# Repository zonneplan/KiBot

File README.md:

# KiBot (formerly KiPlot)

KiBot is a program which helps you to generate the fabrication and
documentation files for your KiCad projects easily, repeatable, and most
of all, scriptably. This means you can use a Makefile to export your
KiCad PCBs just as needed, or do it in a CI/CD environment.

For more information consult the [documentation](https://kibot.readthedocs.io/en/latest/) (hosted by Read the Docs)

If you want to see an example of what KiBot can generate visit this
[project](https://inti-cmnb.github.io/kibot_variants_arduprog_site/Browse/t1-navigate.html)

If this is the first time you read about KiBot, and you prefer to be
introduced listening to a podcast, you can try the following
(english audio, english and spanish subtitles available):

Here is another podcast, more centered on the CI/CD side:

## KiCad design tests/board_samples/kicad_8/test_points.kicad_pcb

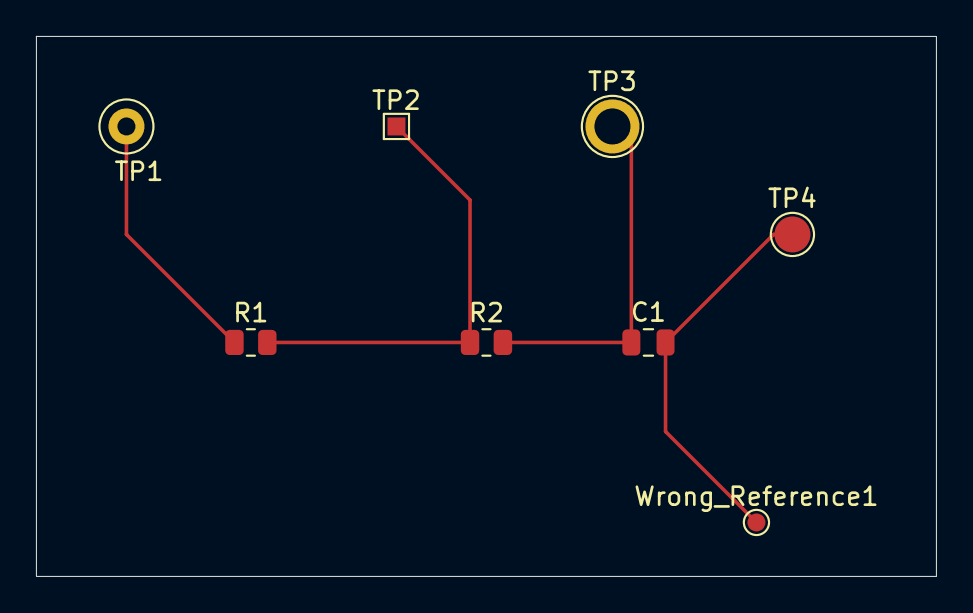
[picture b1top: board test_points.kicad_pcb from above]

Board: 2 copper layers, 50.0 x 30.0 mm, 8 parts (0 on the bottom side), 4 nets.

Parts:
C1: 1uF; C_0805_2012Metric
R1: 10; R_0805_2012Metric
R2: 20; R_0805_2012Metric
TP1: TestPoint; TestPoint_Loop_D1.80mm_Drill1.0mm_Beaded
TP2: TestPoint_Alt; TestPoint_Pad_1.0x1.0mm
TP3: TestPoint_Flag; TestPoint_Plated_Hole_D2.0mm
TP4: TestPoint_Probe; TestPoint_Pad_D2.0mm
Wrong_Reference1: TestPoint_Small; TestPoint_Pad_D1.0mm

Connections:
unnamed: C1.1, R2.2, TP3.1
unnamed: C1.2, TP4.1, Wrong_Reference1.1
unnamed: R1.1, TP1.1
unnamed: R1.2, R2.1, TP2.1

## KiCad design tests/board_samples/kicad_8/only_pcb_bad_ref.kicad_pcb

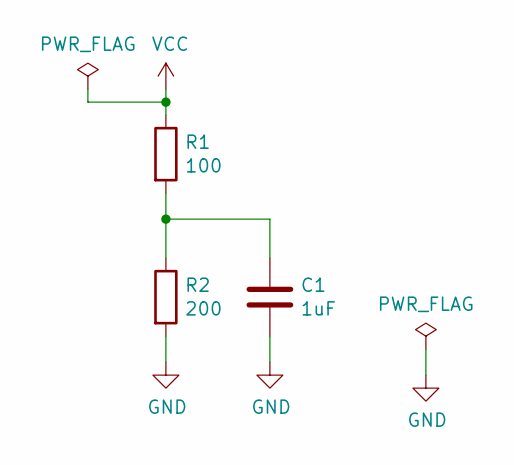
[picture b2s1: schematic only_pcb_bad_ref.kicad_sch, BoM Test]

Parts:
C1: 1uF; C_0805_2012Metric
R1: 100; R_0805_2012Metric
R2: 200; R_0805_2012Metric

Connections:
GND: C1.2, R2.2
unnamed: C1.1, R1.2, R2.1
VCC: R1.1

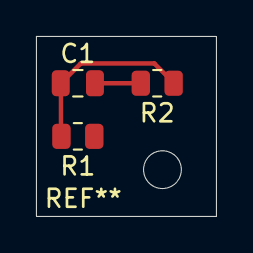
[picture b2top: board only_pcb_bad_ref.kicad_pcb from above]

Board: 2 copper layers, 10.0 x 10.0 mm, 3 parts (0 on the bottom side), 2 nets.

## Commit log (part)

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2024-07-11 [Print PCB][Fixed] Now the layers are always a list
2024-07-11 [iBoM Variants] Better debug info
2024-07-11 [Panelize][Fixed] PanelizeCopperfill.layers initialization
    Members supporting lists must be Optionable
2024-07-11 [Filters][Generic][Fixed] keys processing
    No longer visible as string
2024-07-11 [KiBoM] Simpler lcsc_link code for boolean
2024-07-11 [DOCs][Updated] Filter rotation and generic
2024-07-11 [BoM][Diff] Simplifications now that strings are promoted
2024-07-12 [Preflights] First draft for a fields checker
    See #643
2024-07-15 [Check Fields] Made more configurable the severity actions
2024-07-15 [Render 3D] Made the double trim optional
    Related to #644
2024-07-15 [DOCs] Now preflight docs are in individual documents
2024-07-16 [DOCs] Updated the E/DRC filters explanation
    Fixes #639
2024-07-17 [Windows][macOS] KiCad plug-in detection
    See #642
2024-07-17 [Filters][Added] separate_pins: used to create testpoint reports
    Closes #638
2024-07-17 [Tests] Image Magic site still down
2024-07-19 [DOCs] Separated the filter in individual docs
2024-07-19 [Added] Templates to generate testpoint reports
    Related to #638
2024-08-05 [DOCs] Updated drc_exclusions_workaround help
    Made clear that KiCad 8 solves the original problem.
    See #645
2024-08-05 [Flake8][Fix] C420: Unnecessary dict comprehension
    Rewrite using dict.fromkeys().
2024-08-05 [Tests] ImageMagick site back on line
2024-08-05 [Variants][Fixed] Problems when using `set_text_variables_before_output`
    Fixes #649
2024-08-06 [BoardView][Added] Support for BVR format
    From upstream code
2024-08-06 [Tests] Forced
2024-08-07 [DOCs][Updated] _field_* documentation
2024-08-07 [DOCs][Updated] Options marked as case insensitive
2024-08-07 [Optionable] _init_from_defaults is now the default
2024-08-07 [BoM] Default fit_field is now lowercase
2024-08-07 [DOCs][Updated] Defaults that promote dict -> list(dict)
2024-08-08 [DOCs][Updated] cases where fixed list len was applied
2024-08-08 [GUI][Added] Fixed len lists restrictions
2024-08-09 [GUI][Fixed] list(string)|string initialization issues
    - Renamed to "string_s"
    - Make it use the value from the tree
    - Also forced list(string) DataTypes to use the value from the tree
    - Correctly accept single strings
2024-08-13 [GUI] Sort the list of available preflights
2024-08-14 [DOCs][Updated] Changes in preflight defaults
2024-08-14 [Optionable] Support for [] as default for list(dict)
2024-08-14 [Filters] Moved the compiled regex to _regex
    Cleaner string representation
2024-08-14 [Preflights][Added] String representation
    For cases that aren't just a boolean
2024-08-14 [GUI][Added] dict|list(dict) -> dict_s
2024-08-16 [GUI] When choosing from a list with one element just return it
2024-08-19 [Changed] Stronger workaround for KiCad PCB text cache
    Fixes issues with external tools when not using variants
    Fixes #652
2024-08-19 [Fixed] Pre-flights configured before listing
    Now they have more complex strings that needs configured values
2024-08-19 [Changed] Code to reset the current config moved to a function
2024-08-20 [Changed] Now we keep a copy of the global options tree
2024-08-20 [Changed] extra argument for generate_outputs
    We don't use it
2024-08-20 [GUI][Run][Fixed] Reset the done status before run
2024-08-21 [Added] Dialog to see collected warnings
2024-08-21 [DOCs] Splitted the preflights
    Also sorted the dict types to make it reproducible
2024-08-22 [DOCs][Added] A couple of things KiBot can do
2024-08-22 [DOCs][Internal][Added] Some notes about defaults
2024-08-23 [Fixed] QR Lib output could also remove the exclusions
2024-08-23 [GUI][Fixed] We must ensure the globals are configured
    Not true when no config is loaded
2024-08-23 Allow to detect we never loaded globals
2024-08-23 [GUI][Added] Allow to start without config and/or sch/PCB
2024-08-23 [GUI][Added] Offer to save on exit
2024-08-26 [GUI][Added] Splash screen
    So the user knows we already started
2024-08-26 [GUI][Fixed] PCB file name ... used the SCH
2024-08-27 [GUI] New outputs are created with an unique name and some comment
2024-08-28 [3D Outputs][Fixed] Temporal .kicad_dru file not removed
    Fixes #655
2024-09-02 [GUI][Test] First regression test
    Created injecting events and using a virtual X server
2024-09-05 [GUI][list(string|dict)][Fixed] Initialization
    We need to fill the client data even for strings
2024-09-05 [GUI][Fixed] edited status notification
    Must always reach the parents, we can't assume they have the same
    perspective
2024-09-06 [CI/CD] Unified up/download-artifacts versions (v4)
2024-09-06 [CI/CD][Changed] Now we must explicitly include hidden files
    in artifats
2024-09-09 [DOCs][Filters][Added] error value example
2024-09-09 [Tests][GUI][Added] Preflights test
2024-09-09 [Tests][GUI][Added] Filters test
2024-09-09 [Test][GUI][Added] Variants test
2024-09-10 [Report][Fixed] Division by 0 when no nets are defined
2024-09-11 [Tests][GUI][Added] Groups test
2024-09-12 [Fixed][Render 3D] Rotation/offset for highlighted bottom components
    Fixes #659
2024-09-13 [Tests][CI/CD] Adjust to 8.0.4 render 3d variant 1 test reference
2024-09-13 [GUI] Better incremental search
2024-09-13 [GUI] Adjust the list of groups dialog when adding a new one
2024-09-13 [GUI][Test][Fixed] Problems using standard ids
2024-09-16 [SCH/PCB save][Fixed] Problems with huge constructs
    - In particular zone fills that can be bigger than 1 MB
    - KiCad seems to support lines of upto 1 MB
    - Now we split everything, like KiCad 8 does
    Fixes #660
2024-09-17 [DOCs] Updated docker image versions
2024-09-17 [GUI][Added] Help skeleton
2024-09-18 [DOCs][Updated] CLI options
2024-09-18 [DOCs][Test][Updated] Stats
2024-09-18 [Tests][Added] Separate pins to the GUI filters test
2024-09-18 [DOCs][Fixed] pcbdraw.remap is a string_dict (not a regular dict)
2024-09-18 [GUI][Added] Help for most of the GUI
    JUst opening a browser with the relevant docs section
2024-09-19 [DOCs][Added] Link to podcast introducing KiBot advantages
    AI generated by Google's NotebookLM
2024-09-19 [DOCs][Added] The podcasts to the GitHub README.md
2024-09-19 [DOCs] And another one ...
2024-09-23 [YAML examples][Added] Very simple use of 3D Render top
2024-09-23 [Blender Export][Fixed] Stacked boards
    When using an automatically generated PCB3D
2024-09-24 [PCB Print][Fixed] errors when printing a fully empty layer
2024-09-25 [Updated] KiBot media
2024-09-25 [CI/CD][Release] Changes to avoid deprecation warnings
2024-09-25 [CI/CD][Release][Added] Debug information
    The workflow is currently broken, fails to upload the .deb package
    All seems to be ok, most probably some incompatibility with the
    new artifacts-download (which is really incompatible)
2024-09-27 [CI/CD][Changed] DEB_NAME to uppercase
    Doesn't seem to be needed, but adds coherence
2024-09-27 [PCB Print][Fixed] `repeat_for_layer` with empty `repeat_layers`
    - Is allowed again, this was the old behavior (i.e. 1.7.0)
    - We issue a warning
    Fixes #671
2024-09-30 [GUI] Documented the __init__.py purpose
2024-10-01 [GUI][Added] More spanish translations
2024-10-01 [GUI] Compiled the i18n .mo files
2024-10-05 [SVG Export][Added] Flag for using aux origin
    * Add the same flag from the PDF export for using the aux origin
    for the export.
2024-10-05 [Copy Files][Fixed] Worksheet errors when using from compress
    It affected quick start, the wks was removed and the generated ZIP was
    damaged.
2024-10-07 [DOCs][Changed] The podcast video
    Now with avatars
2024-10-07 [DOCs][Added] Installation instructions using docker
2024-10-07 [DOCs][Added] 370x200 version of the realistic logo
2024-10-07 [DOCs][Updated] podcast link in README.md
2024-10-08 [DOCs][Updated] docker installation
2024-10-08 [DOCs][Installation][Added] How to make the example script executable
2024-10-09 Protect from non-UTF-8 generated by external programs
    I.e. git commits in latin1 encoding
2024-10-10 [CI/CD][Release] Adapted to artifacts v4
2024-10-10 [CI/CD][Tests] Forced
2024-10-14 [DOCs][Added] Script to run Blender from docker images
2024-10-14 [DOCs][Fixed] Variant entries in the index
2024-10-14 [PcbDraw][Fixed] Problems with 0 ohms THT resistors
    When creating the resitor bands
    Fixes #689
2024-10-14 [DOCs][Added] Note about `colored_pads` and `colored_vias` side effects
    Closes #682
2024-10-15 [CI/CD][Test] Forced tests
2024-10-16 [Tests][CI/CD] Adapted to the new Quick Start + KiRi requirements
    Added another commit
2024-10-16 [Worksheet][Added] Undocumented font face and color
    Now can be used, but not correctly rendered
    See #695
2024-10-17 [Fixed] Expansion of internal field names
    KiCad expands "VALUE", not "Value", which is what you see in the GUI
2024-10-17 [Tests][CI/CD][Added] Missing int_bom_simple_sub_pcb.kibot.yaml
2024-10-17 [PCB Print][Fixed] When trying to force a WKS ...
    - And the project didn't define a WKS.
    - The "gui" strategy failed to use the specified WKS
2024-10-18 [DOCs][Removed] File no longer used
2024-10-18 [PCB Print][Fixed] When no WKS is defined
2024-10-21 [PCB Print][Fixed] Stronger workaround for KiCad bug
    The bug that prevents plotting images in worksheets is worst than what
    I though, the plot process is aborted in some cases and you get
    a partial worksheet, not just without images.
2024-10-21 [PCB Print] Documented KiCad bugs
2024-10-21 [PCB Print][Fixed] Cases where force_edge_cuts isn't used
2024-10-21 [Tests][Reference][Updated] Multizone print
    - Now the refill is fixed
    - The center seems to be off, couldn't find a reason
    MIGHT BE A BUG
2024-10-22 [Draw Fancy Stackup] Adjusted the code to match Draw Stackup
    - Applied recent fixes (when creating group)
    - Moved common code
    - Fixed behavior when no vias and draw_vias
    - Fixed flake8 issues
    - Avoided SUColumnsFancy collision
    - Removed VALID_COLUMNS check
2024-10-22 [Tests][GUI][Added][Draw Fancy Stackup] To be expected
2024-10-22 [Download Datasheets][Updated] User agent
    To avoid problems with Zscaler
    Fixes #698
2024-10-22 set make_safe=False sheet and layer_var text expansion to allow colons
2024-10-23 Use GetOrientationDegrees() instead of AsDegrees() for compatiblity with K5/6
2024-10-23 [CI/CD][Dev Images][Fixes] Name of subdir
2024-10-23 [CI/CD][Dev Images] Trying another way to rename
2024-10-23 [DOCs][Added] New global options
    From #700
2024-10-23 Updated alignment (left, center, right) options for K5/6
2024-10-23 parameter typo
2024-10-24 Made the W_DATEFORMAT warning more descriptive
2024-10-24 Centralized the alignment constants in pcb_draw_helpers.py
2024-10-24 [Include Tables][Changed] OutputOptions -> IncTableOutputOptions
    To make it more specific
2024-10-24 [Include Tables][Fixed] Alignment details
    - Moved the numeric version to _text_alignment
    - Always using the constants from pcb_draw_helpers
    - Let Optionable do the text_alignment validation
    - Avoid loading the PCB
2024-10-24 [Include Table][Changed] Small details for maintainability
    - Moved valid output types to a constant
    - Reduced indentation
2024-10-24 [Include Table][Fixed] outputs from strings must be configured
2024-10-24 [Include Table][Changed] Name for the groups
    - To kibot_table_OUTPUT[INDEX]
    - Trying to figure out the CSV name could be challenging
    - Just mentioning the output is much easier
    - In the case of position files separated by side you just need to use
    kibot_table_position[2] for the bottom
2024-10-24 [DOCs][Updated] Including "Include Table"
2024-10-24 [DOCs][Added] Documentation files for "include_table"
2024-10-24 [Include Table][Added] Error when the CSV is missing
2024-10-24 [Include Table][Added] Index range validation
2024-10-24 [DOCs][Include Table] Made the description more clear
2024-10-25 [Tests][Include Table] Adjusted to KiCad 8.0.4
2024-10-28 [CI/CD][Added] workflow dispatch to pythonapp.yml
2024-10-28 [Fix][Include Table] Use correct output parameters w.r.t. CSV files
2024-10-28 [Test][References] Adjusted schematic to 8.0.5
    - The dotted lines are different from 8.0.4
2024-10-28 [CI/CD] Adapted release workflow to the incompatible v4 artifacts
2024-10-29 [Distribution] Also include the KiRi favicon
